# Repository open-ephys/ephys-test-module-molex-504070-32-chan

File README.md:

# Test Module for Molex 504070-based Headstages

This test module works with the Open Ephys
[automated ephys tester](https://github.com/open-ephys/ephys-test-board). 
It can be used to verify the functionality of:

- ONIX Neuropixels 2.0 & Biosignal Headstage

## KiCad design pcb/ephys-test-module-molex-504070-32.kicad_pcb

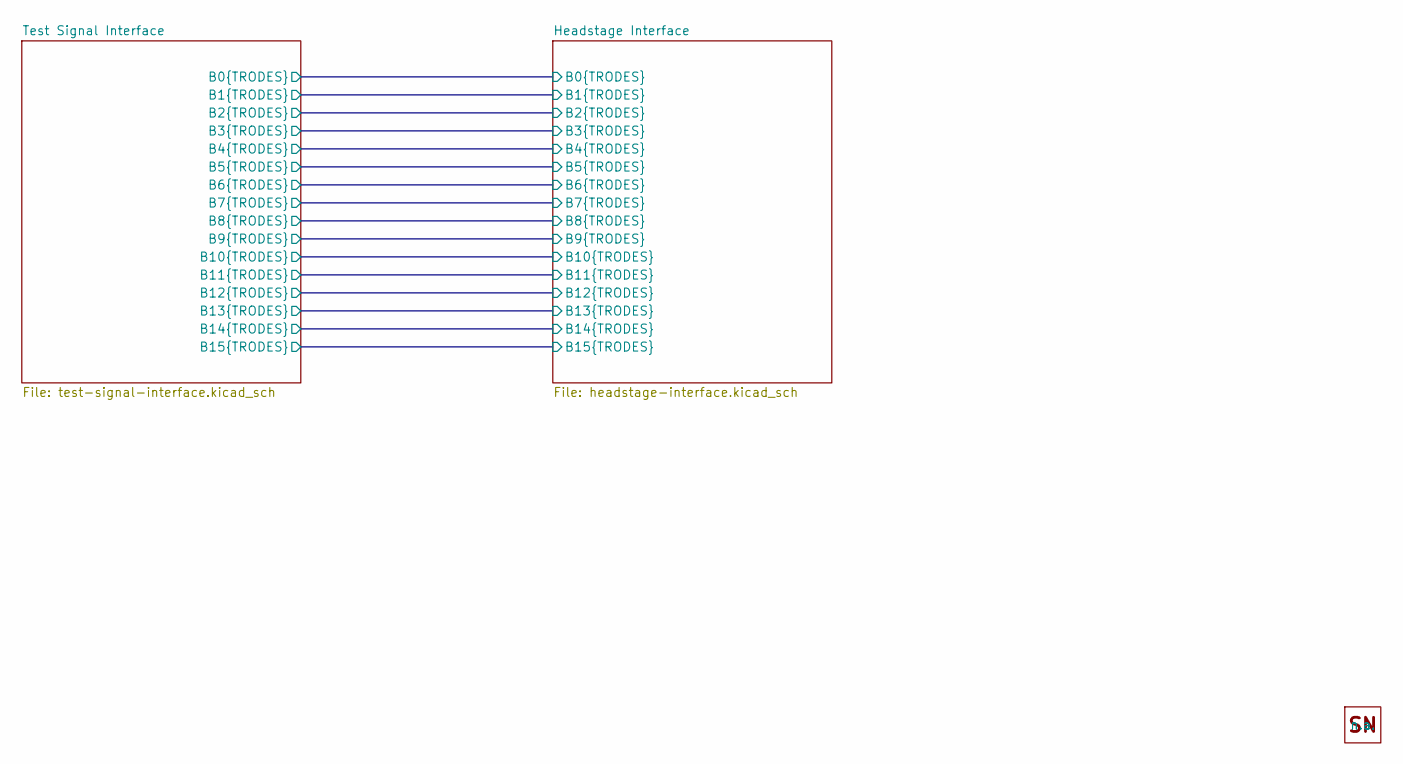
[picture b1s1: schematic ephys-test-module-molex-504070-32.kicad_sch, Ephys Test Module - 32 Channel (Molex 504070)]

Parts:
H1: OEPS_SN-STICKER-8x20mm; MPN n.a.

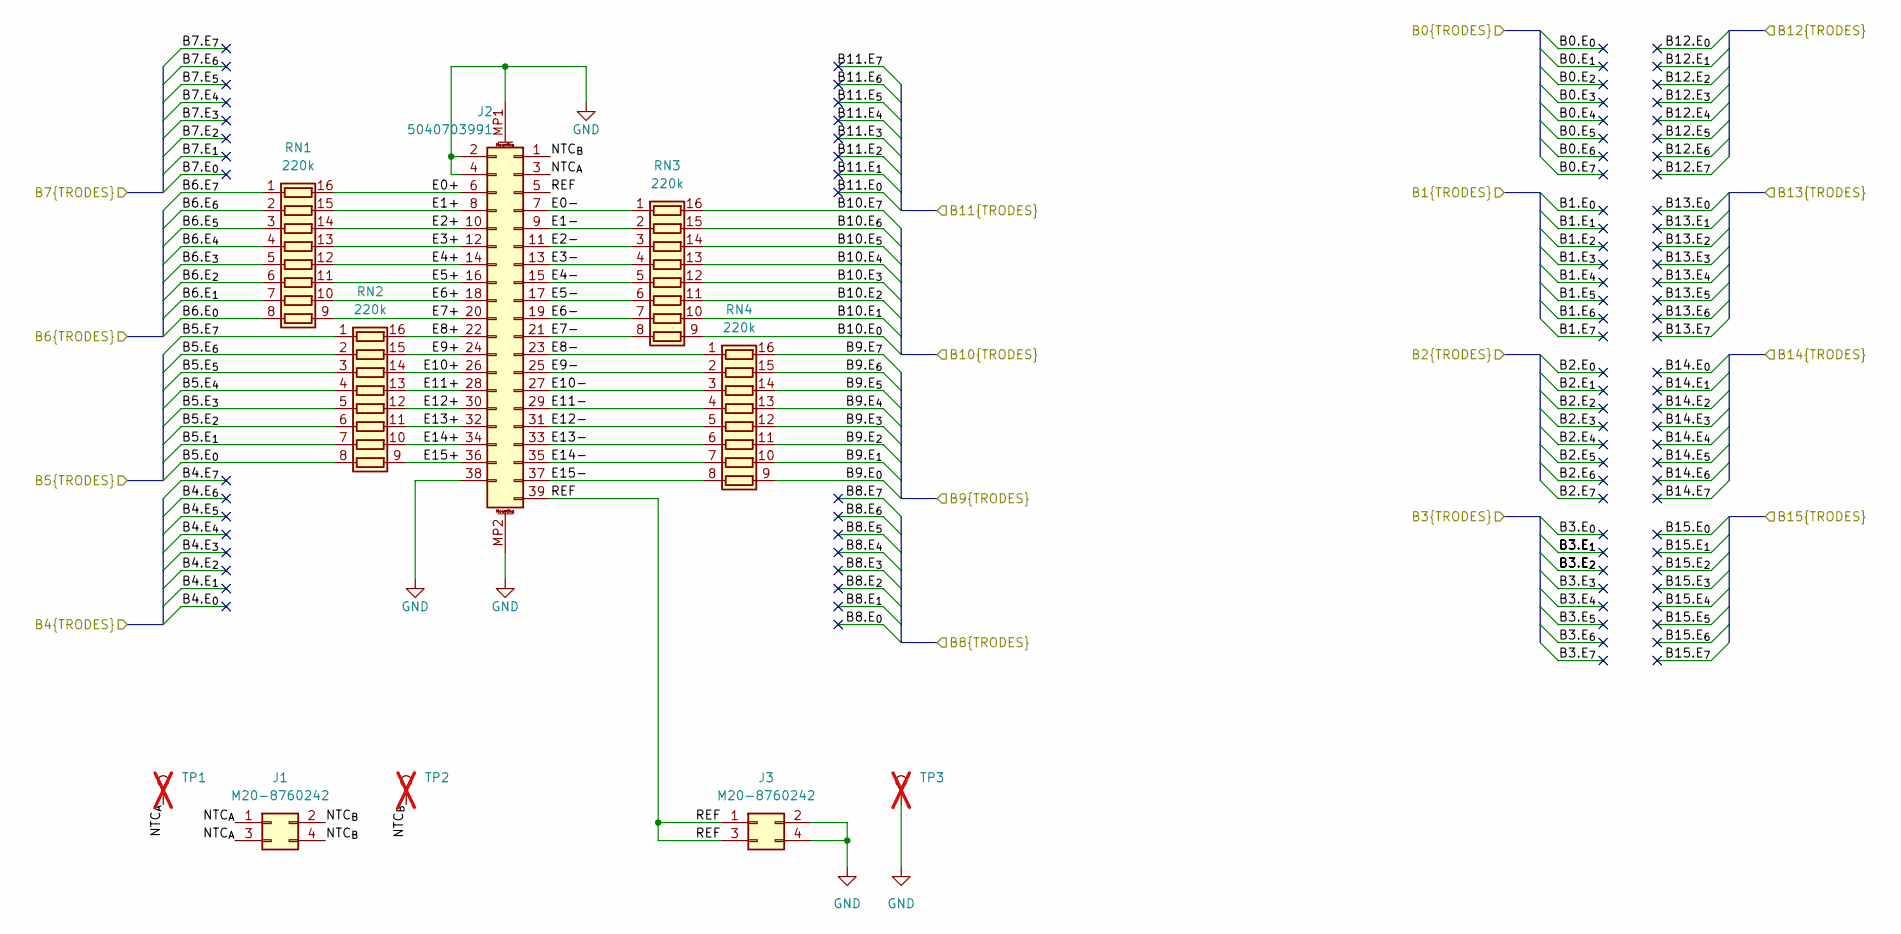
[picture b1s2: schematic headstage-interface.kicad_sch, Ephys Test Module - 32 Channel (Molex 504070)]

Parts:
J1, J3: M20-8760242; PinHeader_2x02_P2.54mm_Vertical_SMD; MPN M20-8760242
J2: 5040703991; MOLEX_5040703991; MPN 5040703991
RN1, RN2, RN3, RN4: 220k; R_Array_Convex_8x0602; Tolerance 5%; MPN YC248-JR-07220KL
TP1: TestPoint; TestPoint_Loop_D3.80mm_Drill2.8mm; MPN n.a.; not fitted
TP2, TP3: TestPoint; TestPoint_Loop_D3.80mm_Drill2.8mm; not fitted

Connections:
/Headstage Interface/B5.E_{0}: RN2.8 (R8.1); also elsewhere on the board
/Headstage Interface/B5.E_{1}: RN2.7 (R7.1); also elsewhere on the board
/Headstage Interface/B5.E_{2}: RN2.6 (R6.1); also elsewhere on the board
/Headstage Interface/B5.E_{3}: RN2.5 (R5.1); also elsewhere on the board
/Headstage Interface/B5.E_{4}: RN2.4 (R4.1); also elsewhere on the board
/Headstage Interface/B5.E_{5}: RN2.3 (R3.1); also elsewhere on the board
/Headstage Interface/B5.E_{6}: RN2.2 (R2.1); also elsewhere on the board
/Headstage Interface/B5.E_{7}: RN2.1 (R1.1); also elsewhere on the board
/Headstage Interface/B6.E_{0}: RN1.8 (R8.1); also elsewhere on the board
/Headstage Interface/B6.E_{1}: RN1.7 (R7.1); also elsewhere on the board
/Headstage Interface/B6.E_{2}: RN1.6 (R6.1); also elsewhere on the board
/Headstage Interface/B6.E_{3}: RN1.5 (R5.1); also elsewhere on the board
/Headstage Interface/B6.E_{4}: RN1.4 (R4.1); also elsewhere on the board
/Headstage Interface/B6.E_{5}: RN1.3 (R3.1); also elsewhere on the board
/Headstage Interface/B6.E_{6}: RN1.2 (R2.1); also elsewhere on the board
/Headstage Interface/B6.E_{7}: RN1.1 (R1.1); also elsewhere on the board
/Headstage Interface/B9.E_{0}: RN4.9 (R8.2); also elsewhere on the board
/Headstage Interface/B9.E_{1}: RN4.10 (R7.2); also elsewhere on the board
/Headstage Interface/B9.E_{2}: RN4.11 (R6.2); also elsewhere on the board
/Headstage Interface/B9.E_{3}: RN4.12 (R5.2); also elsewhere on the board
/Headstage Interface/B9.E_{4}: RN4.13 (R4.2); also elsewhere on the board
/Headstage Interface/B9.E_{5}: RN4.14 (R3.2); also elsewhere on the board
/Headstage Interface/B9.E_{6}: RN4.15 (R2.2); also elsewhere on the board
/Headstage Interface/B9.E_{7}: RN4.16 (R1.2); also elsewhere on the board
/Headstage Interface/B10.E_{0}: RN3.9 (R8.2); also elsewhere on the board
/Headstage Interface/B10.E_{1}: RN3.10 (R7.2); also elsewhere on the board
/Headstage Interface/B10.E_{2}: RN3.11 (R6.2); also elsewhere on the board
/Headstage Interface/B10.E_{3}: RN3.12 (R5.2); also elsewhere on the board
/Headstage Interface/B10.E_{4}: RN3.13 (R4.2); also elsewhere on the board
/Headstage Interface/B10.E_{5}: RN3.14 (R3.2); also elsewhere on the board
/Headstage Interface/B10.E_{6}: RN3.15 (R2.2); also elsewhere on the board
/Headstage Interface/B10.E_{7}: RN3.16 (R1.2); also elsewhere on the board
/Headstage Interface/E0+: J2.6, RN1.16 (R1.2)
/Headstage Interface/E0-: J2.7, RN3.1 (R1.1)
/Headstage Interface/E1+: J2.8, RN1.15 (R2.2)
/Headstage Interface/E1-: J2.9, RN3.2 (R2.1)
/Headstage Interface/E2+: J2.10, RN1.14 (R3.2)
/Headstage Interface/E2-: J2.11, RN3.3 (R3.1)
/Headstage Interface/E3+: J2.12, RN1.13 (R4.2)
/Headstage Interface/E3-: J2.13, RN3.4 (R4.1)
/Headstage Interface/E4+: J2.14, RN1.12 (R5.2)
/Headstage Interface/E4-: J2.15, RN3.5 (R5.1)
/Headstage Interface/E5+: J2.16, RN1.11 (R6.2)
/Headstage Interface/E5-: J2.17, RN3.6 (R6.1)
/Headstage Interface/E6+: J2.18, RN1.10 (R7.2)
/Headstage Interface/E6-: J2.19, RN3.7 (R7.1)
/Headstage Interface/E7+: J2.20, RN1.9 (R8.2)
/Headstage Interface/E7-: J2.21, RN3.8 (R8.1)
/Headstage Interface/E8+: J2.22, RN2.16 (R1.2)
/Headstage Interface/E8-: J2.23, RN4.1 (R1.1)
/Headstage Interface/E9+: J2.24, RN2.15 (R2.2)
/Headstage Interface/E9-: J2.25, RN4.2 (R2.1)
/Headstage Interface/E10+: J2.26, RN2.14 (R3.2)
/Headstage Interface/E10-: J2.27, RN4.3 (R3.1)
/Headstage Interface/E11+: J2.28, RN2.13 (R4.2)
/Headstage Interface/E11-: J2.29, RN4.4 (R4.1)
/Headstage Interface/E12+: J2.30, RN2.12 (R5.2)
/Headstage Interface/E12-: J2.31, RN4.5 (R5.1)
/Headstage Interface/E13+: J2.32, RN2.11 (R6.2)
/Headstage Interface/E13-: J2.33 (Pin_31), RN4.6 (R6.1)
/Headstage Interface/E14+: J2.34 (Pin_32), RN2.10 (R7.2)
/Headstage Interface/E14-: J2.35 (Pin_31), RN4.7 (R7.1)
/Headstage Interface/E15+: J2.36 (Pin_32), RN2.9 (R8.2)
/Headstage Interface/E15-: J2.37 (Pin_31), RN4.8 (R8.1)
/Headstage Interface/NTC_{A}: J1.1, J1.3, J2.3, TP1.1
/Headstage Interface/NTC_{B}: J1.2, J1.4, J2.1, TP2.1
/Headstage Interface/REF: J2.5, J2.39 (Pin_31), J3.1, J3.3
GND: J2.2, J2.4, J2.38 (Pin_32), J2.MP1 (MountPin1), J2.MP2 (MountPin2), J3.2, J3.4, TP3.1; also elsewhere on the board

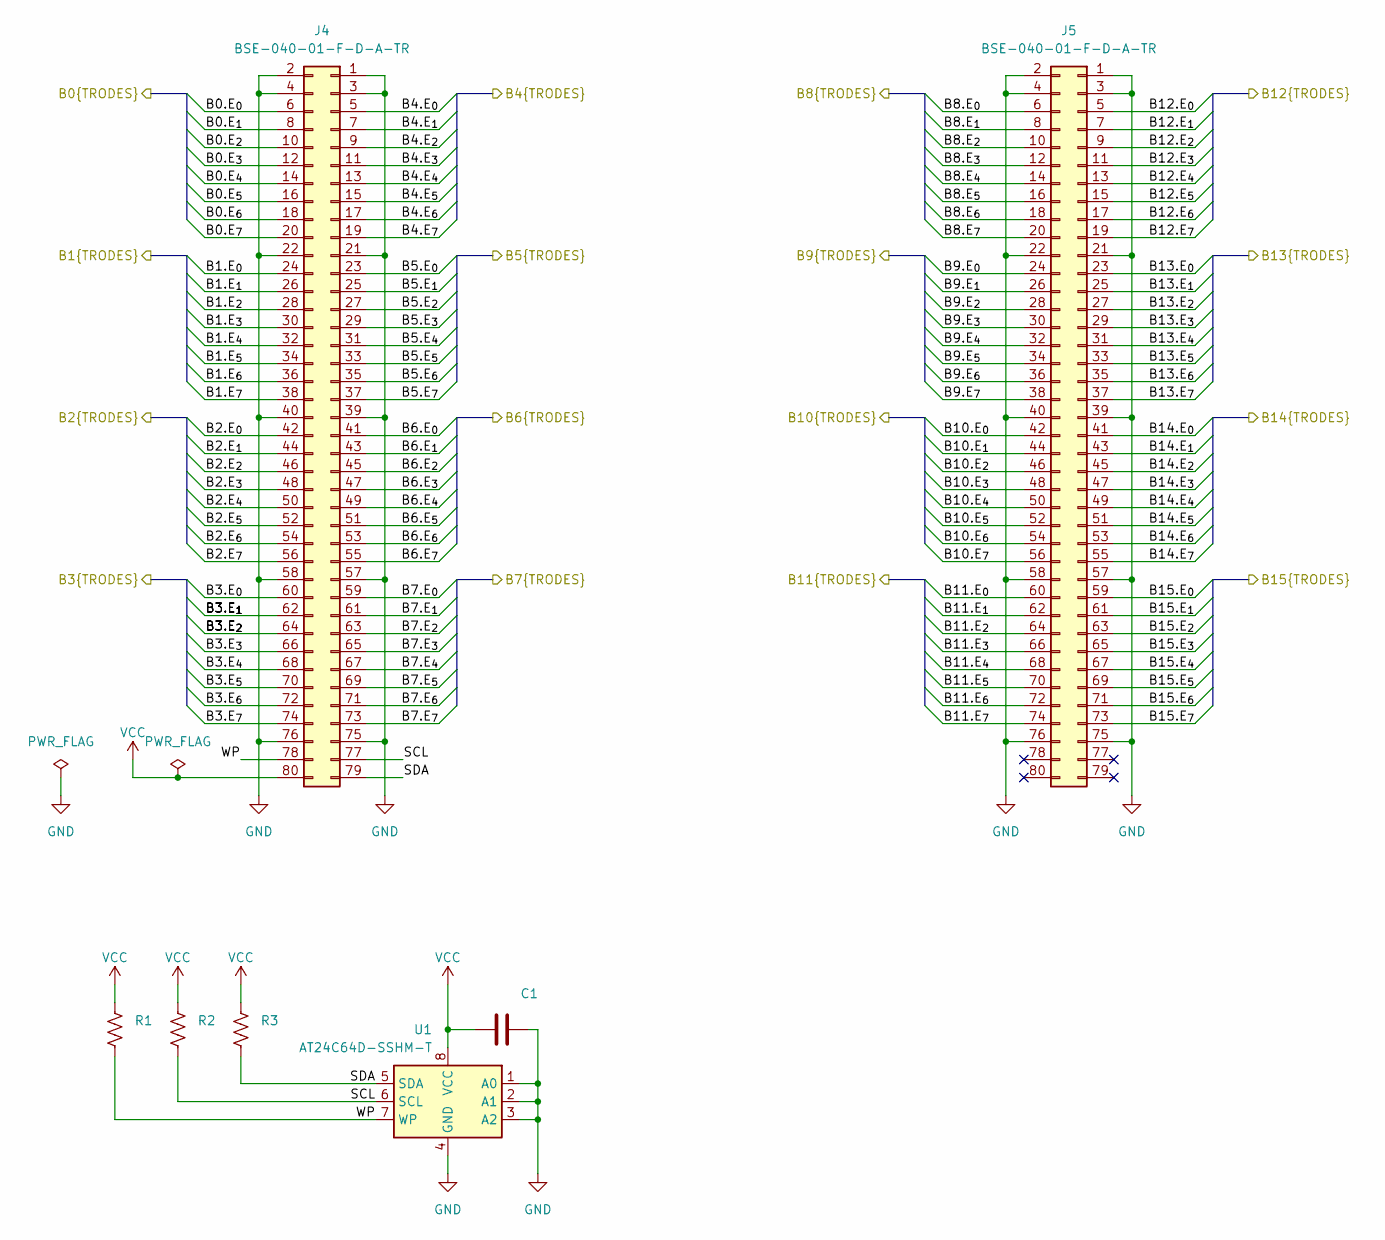
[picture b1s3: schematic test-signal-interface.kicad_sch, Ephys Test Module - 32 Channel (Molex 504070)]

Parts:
C1: 100nF; C_0402_1005Metric; Tolerance 10%; MPN C1005X5R1V104K050BB
J4, J5: BSE-040-01-F-D-A-TR; SAMTEC_BSE-040-01-X-D-A; MPN BSE-040-01-F-D-A-TR
R1, R2, R3: 1k; R_0402_1005Metric; Tolerance 1%; MPN CRCW04021K00FKED
U1: AT24C64D-SSHM-T; SOIC-8_3.9x4.9mm_P1.27mm; MPN AT24C64D-SSHM-T

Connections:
/Headstage Interface/B0.E_{0}: J4.6
/Headstage Interface/B0.E_{1}: J4.8
/Headstage Interface/B0.E_{2}: J4.10
/Headstage Interface/B0.E_{3}: J4.12
/Headstage Interface/B0.E_{4}: J4.14
/Headstage Interface/B0.E_{5}: J4.16
/Headstage Interface/B0.E_{6}: J4.18
/Headstage Interface/B0.E_{7}: J4.20
/Headstage Interface/B1.E_{0}: J4.24
/Headstage Interface/B1.E_{1}: J4.26
/Headstage Interface/B1.E_{2}: J4.28
/Headstage Interface/B1.E_{3}: J4.30
/Headstage Interface/B1.E_{4}: J4.32
/Headstage Interface/B1.E_{5}: J4.34
/Headstage Interface/B1.E_{6}: J4.36
/Headstage Interface/B1.E_{7}: J4.38
/Headstage Interface/B2.E_{0}: J4.42
/Headstage Interface/B2.E_{1}: J4.44
/Headstage Interface/B2.E_{2}: J4.46
/Headstage Interface/B2.E_{3}: J4.48
/Headstage Interface/B2.E_{4}: J4.50
/Headstage Interface/B2.E_{5}: J4.52
/Headstage Interface/B2.E_{6}: J4.54
/Headstage Interface/B2.E_{7}: J4.56
/Headstage Interface/B3.E_{0}: J4.60
/Headstage Interface/B3.E_{1}: J4.62
/Headstage Interface/B3.E_{2}: J4.64
/Headstage Interface/B3.E_{3}: J4.66
/Headstage Interface/B3.E_{4}: J4.68
/Headstage Interface/B3.E_{5}: J4.70
/Headstage Interface/B3.E_{6}: J4.72
/Headstage Interface/B3.E_{7}: J4.74
/Headstage Interface/B4.E_{0}: J4.5
/Headstage Interface/B4.E_{1}: J4.7
/Headstage Interface/B4.E_{2}: J4.9
/Headstage Interface/B4.E_{3}: J4.11
/Headstage Interface/B4.E_{4}: J4.13
/Headstage Interface/B4.E_{5}: J4.15
/Headstage Interface/B4.E_{6}: J4.17
/Headstage Interface/B4.E_{7}: J4.19
/Headstage Interface/B5.E_{0}: J4.23; also elsewhere on the board
/Headstage Interface/B5.E_{1}: J4.25; also elsewhere on the board
/Headstage Interface/B5.E_{2}: J4.27; also elsewhere on the board
/Headstage Interface/B5.E_{3}: J4.29; also elsewhere on the board
/Headstage Interface/B5.E_{4}: J4.31; also elsewhere on the board
/Headstage Interface/B5.E_{5}: J4.33; also elsewhere on the board
/Headstage Interface/B5.E_{6}: J4.35; also elsewhere on the board
/Headstage Interface/B5.E_{7}: J4.37; also elsewhere on the board
/Headstage Interface/B6.E_{0}: J4.41; also elsewhere on the board
/Headstage Interface/B6.E_{1}: J4.43; also elsewhere on the board
/Headstage Interface/B6.E_{2}: J4.45; also elsewhere on the board
/Headstage Interface/B6.E_{3}: J4.47; also elsewhere on the board
/Headstage Interface/B6.E_{4}: J4.49; also elsewhere on the board
/Headstage Interface/B6.E_{5}: J4.51; also elsewhere on the board
/Headstage Interface/B6.E_{6}: J4.53; also elsewhere on the board
/Headstage Interface/B6.E_{7}: J4.55; also elsewhere on the board
/Headstage Interface/B7.E_{0}: J4.59
/Headstage Interface/B7.E_{1}: J4.61
/Headstage Interface/B7.E_{2}: J4.63
/Headstage Interface/B7.E_{3}: J4.65
/Headstage Interface/B7.E_{4}: J4.67
/Headstage Interface/B7.E_{5}: J4.69
/Headstage Interface/B7.E_{6}: J4.71
/Headstage Interface/B7.E_{7}: J4.73
/Headstage Interface/B8.E_{0}: J5.6
/Headstage Interface/B8.E_{1}: J5.8
/Headstage Interface/B8.E_{2}: J5.10
/Headstage Interface/B8.E_{3}: J5.12
/Headstage Interface/B8.E_{4}: J5.14
/Headstage Interface/B8.E_{5}: J5.16
/Headstage Interface/B8.E_{6}: J5.18
/Headstage Interface/B8.E_{7}: J5.20
/Headstage Interface/B9.E_{0}: J5.24; also elsewhere on the board
/Headstage Interface/B9.E_{1}: J5.26; also elsewhere on the board
/Headstage Interface/B9.E_{2}: J5.28; also elsewhere on the board
/Headstage Interface/B9.E_{3}: J5.30; also elsewhere on the board
/Headstage Interface/B9.E_{4}: J5.32; also elsewhere on the board
/Headstage Interface/B9.E_{5}: J5.34; also elsewhere on the board
/Headstage Interface/B9.E_{6}: J5.36; also elsewhere on the board
/Headstage Interface/B9.E_{7}: J5.38; also elsewhere on the board
/Headstage Interface/B10.E_{0}: J5.42; also elsewhere on the board
/Headstage Interface/B10.E_{1}: J5.44; also elsewhere on the board
/Headstage Interface/B10.E_{2}: J5.46; also elsewhere on the board
/Headstage Interface/B10.E_{3}: J5.48; also elsewhere on the board
/Headstage Interface/B10.E_{4}: J5.50; also elsewhere on the board
/Headstage Interface/B10.E_{5}: J5.52; also elsewhere on the board
/Headstage Interface/B10.E_{6}: J5.54; also elsewhere on the board
/Headstage Interface/B10.E_{7}: J5.56; also elsewhere on the board
/Headstage Interface/B11.E_{0}: J5.60
/Headstage Interface/B11.E_{1}: J5.62
/Headstage Interface/B11.E_{2}: J5.64
/Headstage Interface/B11.E_{3}: J5.66
/Headstage Interface/B11.E_{4}: J5.68
/Headstage Interface/B11.E_{5}: J5.70
/Headstage Interface/B11.E_{6}: J5.72
/Headstage Interface/B11.E_{7}: J5.74
/Headstage Interface/B12.E_{0}: J5.5
/Headstage Interface/B12.E_{1}: J5.7
/Headstage Interface/B12.E_{2}: J5.9
/Headstage Interface/B12.E_{3}: J5.11
/Headstage Interface/B12.E_{4}: J5.13
/Headstage Interface/B12.E_{5}: J5.15
/Headstage Interface/B12.E_{6}: J5.17
/Headstage Interface/B12.E_{7}: J5.19
/Headstage Interface/B13.E_{0}: J5.23
/Headstage Interface/B13.E_{1}: J5.25
/Headstage Interface/B13.E_{2}: J5.27
/Headstage Interface/B13.E_{3}: J5.29
/Headstage Interface/B13.E_{4}: J5.31
/Headstage Interface/B13.E_{5}: J5.33
/Headstage Interface/B13.E_{6}: J5.35
/Headstage Interface/B13.E_{7}: J5.37
/Headstage Interface/B14.E_{0}: J5.41
/Headstage Interface/B14.E_{1}: J5.43
/Headstage Interface/B14.E_{2}: J5.45
/Headstage Interface/B14.E_{3}: J5.47
/Headstage Interface/B14.E_{4}: J5.49
/Headstage Interface/B14.E_{5}: J5.51
/Headstage Interface/B14.E_{6}: J5.53
/Headstage Interface/B14.E_{7}: J5.55
/Headstage Interface/B15.E_{0}: J5.59
/Headstage Interface/B15.E_{1}: J5.61
/Headstage Interface/B15.E_{2}: J5.63
/Headstage Interface/B15.E_{3}: J5.65
/Headstage Interface/B15.E_{4}: J5.67
/Headstage Interface/B15.E_{5}: J5.69
/Headstage Interface/B15.E_{6}: J5.71
/Headstage Interface/B15.E_{7}: J5.73
/Test Signal Interface/SCL: J4.77, R2.2, U1.6 (SCL)
/Test Signal Interface/SDA: J4.79, R3.2, U1.5 (SDA)
/Test Signal Interface/WP: J4.78, R1.2, U1.7 (WP)
GND: C1.2, J4.1, J4.2, J4.3, J4.4, J4.21, J4.22, J4.39, J4.40, J4.57, J4.58, J4.75, J4.76, J5.1, J5.2, J5.3, J5.4, J5.21, J5.22, J5.39, J5.40, J5.57, J5.58, J5.75, J5.76, U1.1 (A0), U1.2 (A1), U1.3 (A2), U1.4 (GND); also elsewhere on the board
VCC: C1.1, J4.80, R1.1, R2.1, R3.1, U1.8 (VCC)

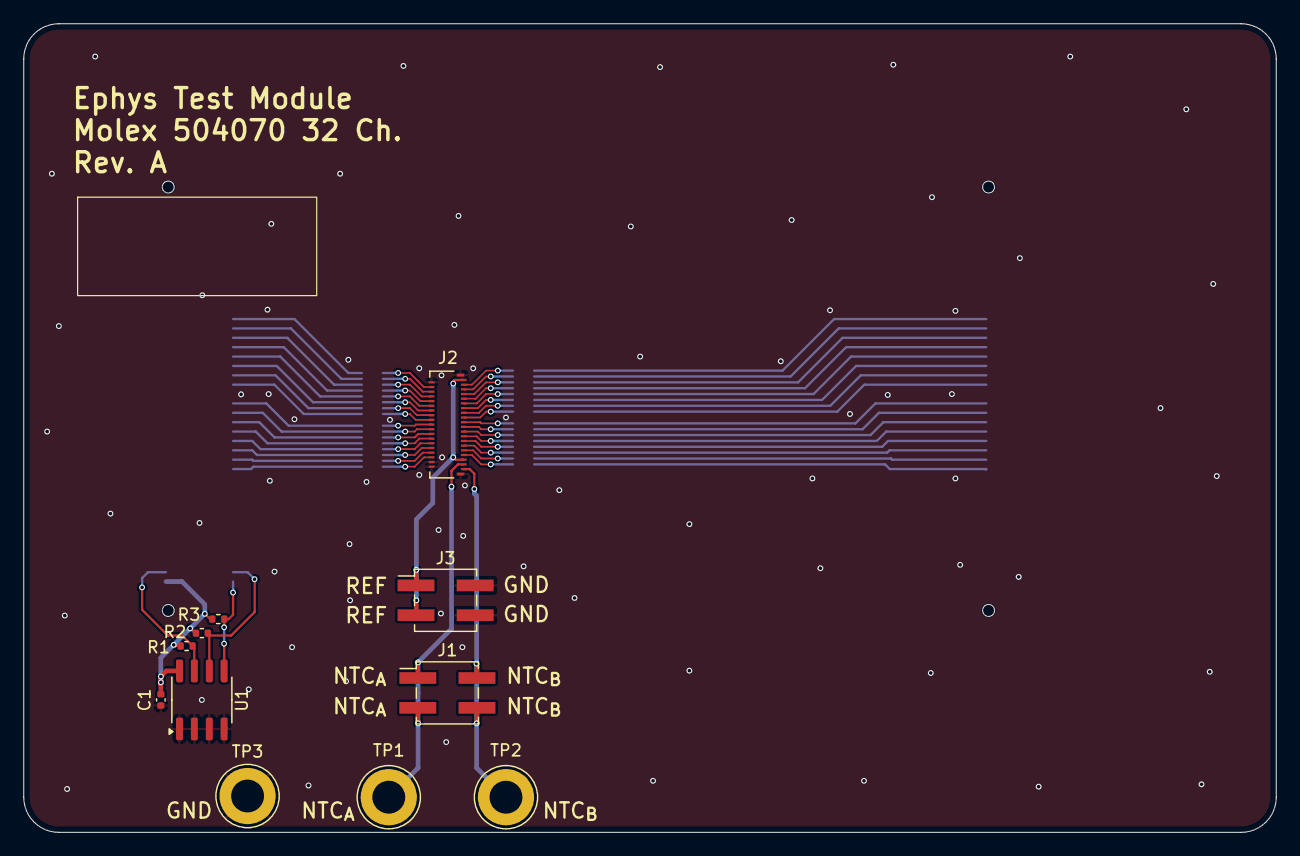
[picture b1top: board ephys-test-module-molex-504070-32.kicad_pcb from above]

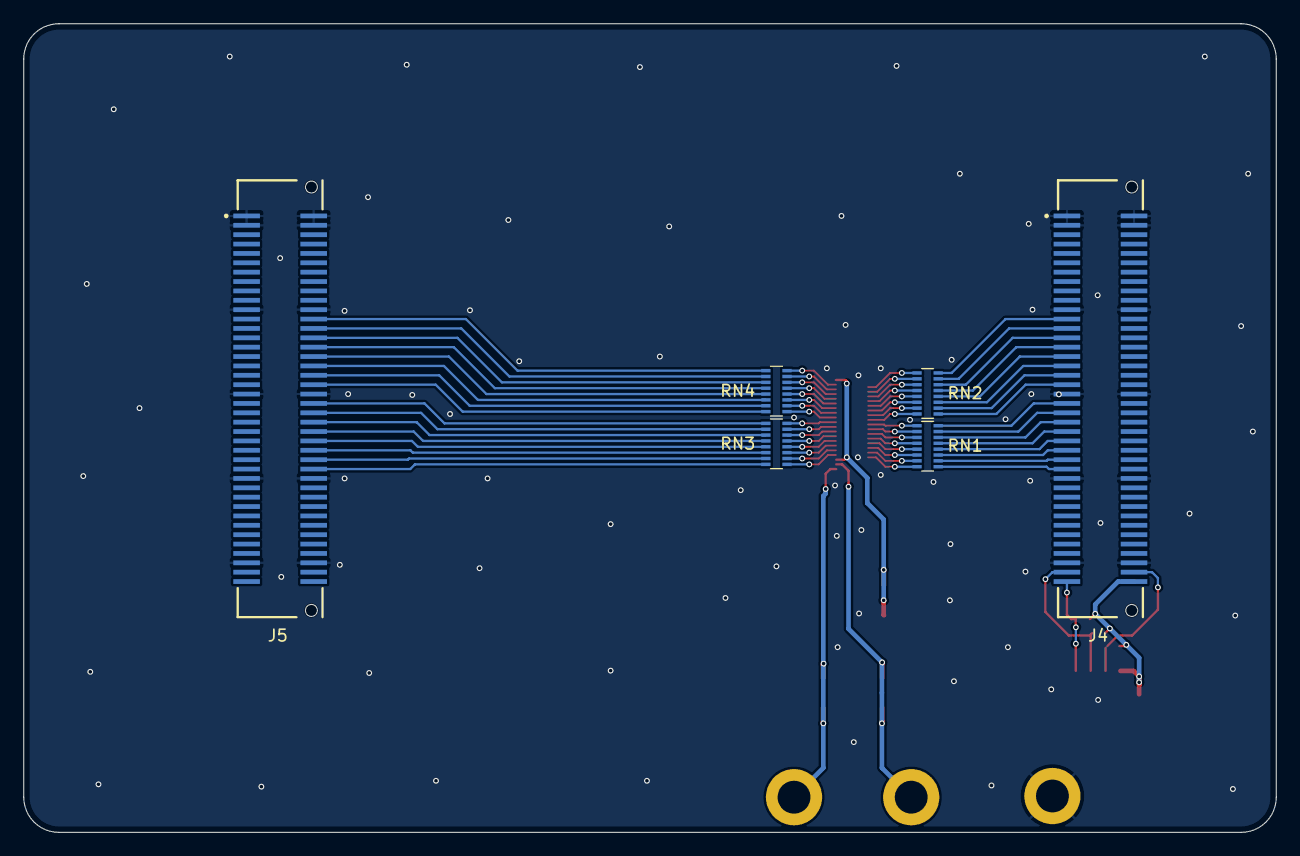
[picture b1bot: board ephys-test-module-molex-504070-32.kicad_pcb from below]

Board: 2 copper layers, 106.9 x 69.0 mm, 18 parts (6 on the bottom side), 72 nets.

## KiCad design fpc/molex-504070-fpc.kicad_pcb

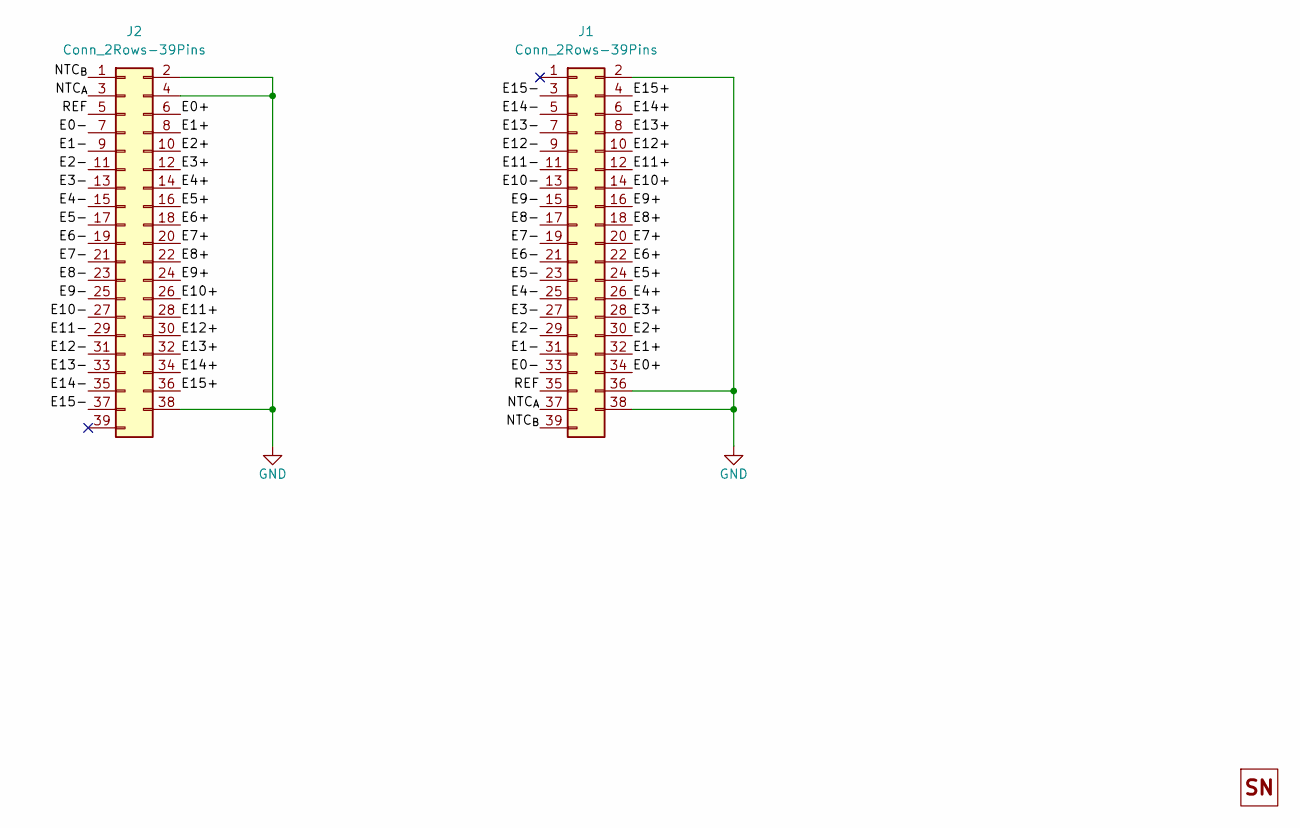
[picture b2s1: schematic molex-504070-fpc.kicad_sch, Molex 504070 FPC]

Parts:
H1: OEPS_SN-STICKER-5x5mm; MPN n.a.
J1, J2: Conn_2Rows-39Pins; MOLEX_5040703991_FPC-mate_low-spec

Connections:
/E0+: J1.34, J2.6
/E0-: J1.33, J2.7
/E1+: J1.32, J2.8
/E1-: J1.31, J2.9
/E2+: J1.30, J2.10
/E2-: J1.29, J2.11
/E3+: J1.28, J2.12
/E3-: J1.27, J2.13
/E4+: J1.26, J2.14
/E4-: J1.25, J2.15
/E5+: J1.24, J2.16
/E5-: J1.23, J2.17
/E6+: J1.22, J2.18
/E6-: J1.21, J2.19
/E7+: J1.20, J2.20
/E7-: J1.19, J2.21
/E8+: J1.18, J2.22
/E8-: J1.17, J2.23
/E9+: J1.16, J2.24
/E9-: J1.15, J2.25
/E10+: J1.14, J2.26
/E10-: J1.13, J2.27
/E11+: J1.12, J2.28
/E11-: J1.11, J2.29
/E12+: J1.10, J2.30
/E12-: J1.9, J2.31
/E13+: J1.8, J2.32
/E13-: J1.7, J2.33
/E14+: J1.6, J2.34
/E14-: J1.5, J2.35
/E15+: J1.4, J2.36
/E15-: J1.3, J2.37
/NTC_{A}: J1.37, J2.3
/NTC_{B}: J1.39, J2.1
/REF: J1.35, J2.5
GND: J1.2, J1.36, J1.38, J2.2, J2.4, J2.38

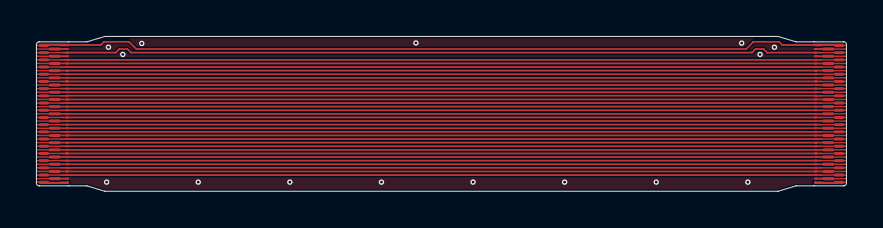
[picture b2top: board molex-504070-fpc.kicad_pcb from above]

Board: 2 copper layers, 45.0 x 8.6 mm, 3 parts (0 on the bottom side), 36 nets.

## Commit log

2026-01-13 Update README
    - Fix connector name
2026-01-21 Revision A candidate
    - Also, added an mating FPC design to connect the test module to the
    headstage
2026-05-27 Add an SVG of the headtage-side FPC pinout
